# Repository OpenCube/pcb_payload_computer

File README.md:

OpenCube Payload Computer
=========================

The OpenCube Payload Computer is composed of a Base Unit (MSP430) and an Atmega. The Base Unit is making the link between the CDMU and the Atmega and allows plug&play with the CDMU.

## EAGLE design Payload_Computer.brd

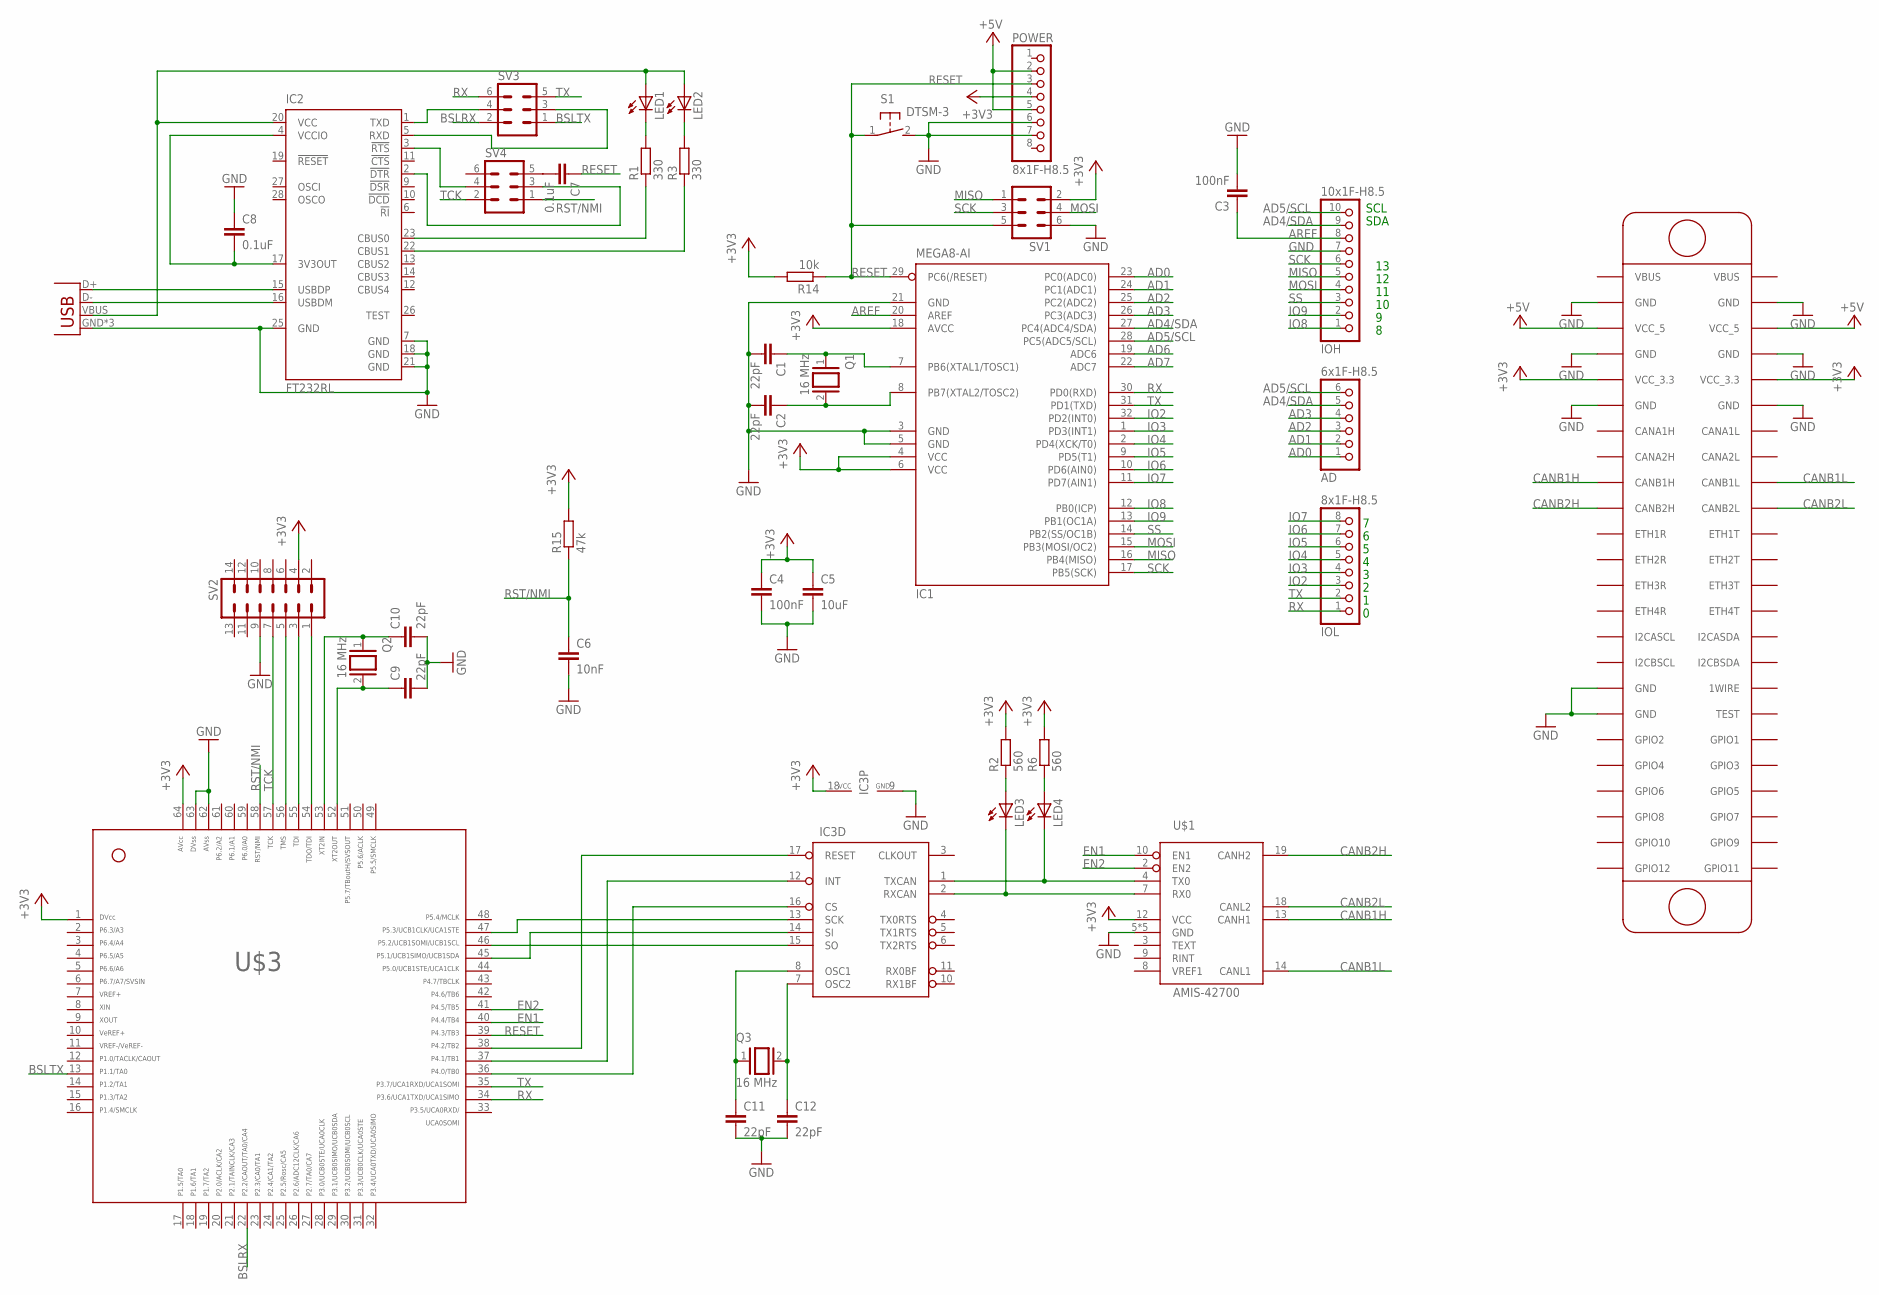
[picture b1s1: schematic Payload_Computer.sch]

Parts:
AD: 6x1F-H8.5; 1X06
C1, C2, C9, C10, C11, C12: 22pF; C0805
C3, C4: 100nF; C0805
C5: 10uF; C0805
C6: 10nF; C0805
C7, C8: 0.1uF; C0805
IC1: MEGA8-AI; TQFP32-08
IC2: FT232RL; SSOP28
IC3: MCP2515SO; SO-18W
IOH: 10x1F-H8.5; 1X10
IOL: 8x1F-H8.5; 1X08
JP1: USB-MICROB
LED1, LED2, LED3, LED4: LED3MM
POWER: 8x1F-H8.5; 1X08
Q1, Q2, Q3: 16 MHz; QS
R1, R3: 330; R0805
R2, R6: 560; R0805
R14: 10k; R0805
R15: 47k; R0805
S1: DTSM-3
SV1, SV3, SV4: MA03-2
SV2: MA07-2
U$1: AMIS-42700; SOIC20
U$2: CUBESAT_PCB
U$3: F241X---PM64; PM/PAG64

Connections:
+3V3: C4.1, C5.1, IC1.4 (VCC), IC1.6 (VCC), IC1.18 (AVCC), IC3.18 (VCC), POWER.4, R2.2, R6.2, R14.2, R15.2, SV1.2, SV2.4, U$1.12 (VCC), U$2.VCC_3.3@1 (VCC_3.3), U$2.VCC_3.3@2 (VCC_3.3), U$3.1, U$3.64
+5V: POWER.2, POWER.5, U$2.VCC_5@1 (VCC_5), U$2.VCC_5@2 (VCC_5)
AD0: AD.1, IC1.23 (PC0(ADC0))
AD1: AD.2, IC1.24 (PC1(ADC1))
AD2: AD.3, IC1.25 (PC2(ADC2))
AD3: AD.4, IC1.26 (PC3(ADC3))
AD4/SDA: AD.5, IC1.27 (PC4(ADC4/SDA)), IOH.9
AD5/SCL: AD.6, IC1.28 (PC5(ADC5/SCL)), IOH.10
AD6: IC1.19 (ADC6)
AD7: IC1.22 (ADC7)
AREF: C3.1, IC1.20 (AREF), IOH.8
BSLRX: SV3.2, U$3.22
BSLTX: SV3.1, U$3.13
CANB1H: U$1.13 (CANH1), U$2.CANB1H
CANB1L: U$1.14 (CANL1), U$2.CANB1L
CANB2H: U$1.19 (CANH2), U$2.CANB2H
CANB2L: U$1.18 (CANL2), U$2.CANB2L
EN1: U$1.10 (EN1), U$3.40
EN2: U$1.2 (EN2), U$3.41
GND: C1.2, C2.2, C3.2, C4.2, C5.2, C6.2, C8.1, C9.2, C10.2, C11.2, C12.2, IC1.3 (GND), IC1.5 (GND), IC1.21 (GND), IC2.7 (GND), IC2.18 (GND), IC2.21 (GND), IC2.25 (GND), IC3.9 (GND), IOH.7, JP1.GND, JP1.MT1 (GND), JP1.MT2 (GND), POWER.6, POWER.7, S1.2, SV1.6, SV2.9, U$1.5 (GND), U$1.6 (GND), U$1.15 (GND), U$1.16 (GND), U$1.17 (GND), U$2.GND@5 (GND), U$2.GND@6 (GND), U$2.GND@7 (GND), U$2.GND@8 (GND), U$2.GND@9 (GND), U$2.GND@10 (GND), U$2.GND@11 (GND), U$2.GND@12 (GND), U$3.62, U$3.63
IO2: IC1.32 (PD2(INT0)), IOL.3
IO3: IC1.1 (PD3(INT1)), IOL.4
IO4: IC1.2 (PD4(XCK/T0)), IOL.5
IO5: IC1.9 (PD5(T1)), IOL.6
IO6: IC1.10 (PD6(AIN0)), IOL.7
IO7: IC1.11 (PD7(AIN1)), IOL.8
IO8: IC1.12 (PB0(ICP)), IOH.1
IO9: IC1.13 (PB1(OC1A)), IOH.2
MISO: IC1.16 (PB4(MISO)), IOH.5, SV1.1
MOSI: IC1.15 (PB3(MOSI/OC2)), IOH.4, SV1.4
unnamed: IC3.1 (TXCAN), LED4.K (C), U$1.4 (TX0)
unnamed: C12.1, IC3.7 (OSC2), Q3.2
unnamed: IC3.2 (RXCAN), LED3.K (C), U$1.7 (RX0)
unnamed: C8.2, IC2.4 (VCCIO), IC2.17 (3V3OUT)
unnamed: IC2.15 (USBDP), JP1.D+
unnamed: IC2.16 (USBDM), JP1.D-
unnamed: IC2.20 (VCC), JP1.VBUS, LED1.A, LED2.A
unnamed: LED1.K (C), R1.2
unnamed: LED2.K (C), R3.2
unnamed: IC2.23 (CBUS0), R1.1
unnamed: IC2.22 (CBUS1), R3.1
unnamed: LED3.A, R2.1
unnamed: LED4.A, R6.1
unnamed: C7.2, SV4.5
unnamed: IC2.1 (TXD), SV3.4
unnamed: IC2.5 (RXD), SV3.3
unnamed: IC2.2 (!DTR), SV4.3
unnamed: C1.1, IC1.7 (PB6(XTAL1/TOSC1)), Q1.1
unnamed: C2.1, IC1.8 (PB7(XTAL2/TOSC2)), Q1.2
unnamed: C11.1, IC3.8 (OSC1), Q3.1
unnamed: SV2.1, U$3.54
unnamed: SV2.3, U$3.55
unnamed: SV2.5, U$3.56
unnamed: IC2.3 (!RTS), SV4.4
unnamed: IC3.15 (SO), U$3.46
unnamed: IC3.14 (SI), U$3.45
unnamed: IC3.13 (SCK), U$3.47
unnamed: IC3.16 (CS), U$3.36
unnamed: IC3.12 (INT), U$3.37
unnamed: IC3.17 (RESET), U$3.38
RESET: C7.1, IC1.29 (PC6(/RESET)), POWER.3, R14.1, S1.1, SV1.5, U$3.39
RST/NMI: C6.1, R15.1, SV4.1, U$3.58
RX: IC1.30 (PD0(RXD)), IOL.1, SV3.6, U$3.34
SCK: IC1.17 (PB5(SCK)), IOH.6, SV1.3
SS: IC1.14 (PB2(SS/OC1B)), IOH.3
TCK: SV2.7, SV4.2, U$3.57
TX: IC1.31 (PD1(TXD)), IOL.2, SV3.5, U$3.35
XT2IN: C10.1, Q2.1, U$3.53
XT2OUT: C9.1, Q2.2, U$3.52

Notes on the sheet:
SDA
SCL

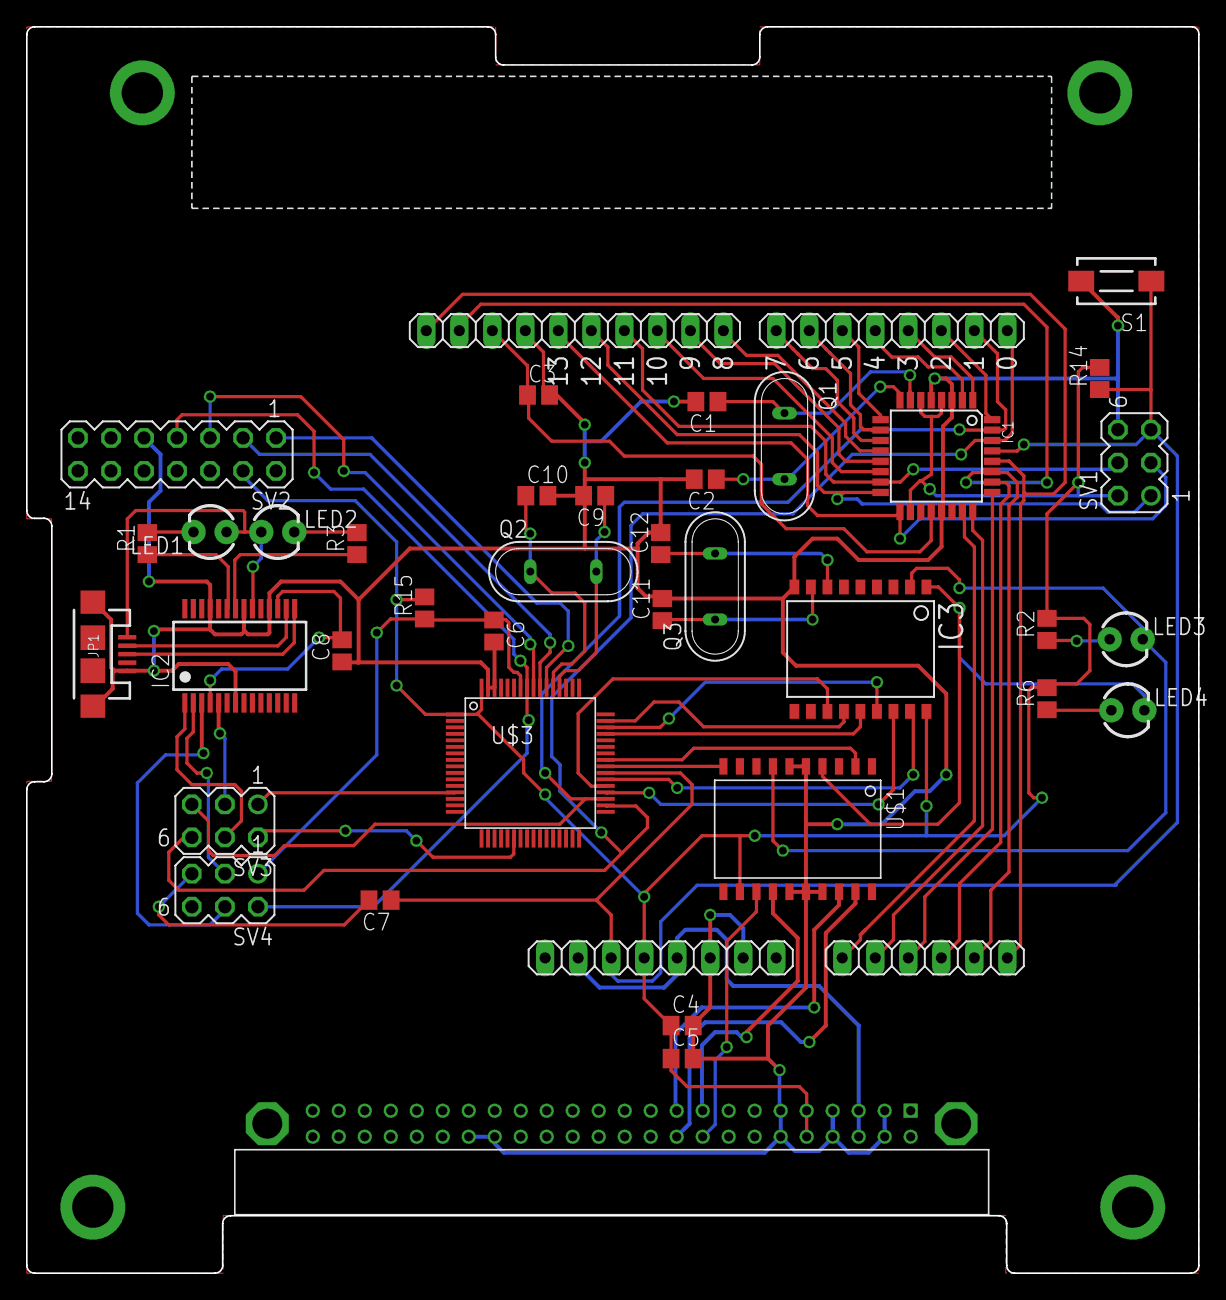
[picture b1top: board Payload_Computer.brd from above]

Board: 2 copper layers, 90.2 x 95.9 mm, 41 parts (0 on the bottom side), 67 nets.

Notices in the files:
parts and their libraries:
SparkFun-Connectors: Licensing: CC v3.0 Share-Alike You are welcome to use this library for commercial purposes.
